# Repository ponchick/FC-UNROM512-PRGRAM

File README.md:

# FC-UNROM512

UNROM512 Famicom cartridge PCB (UNROM/UOROM family, extended PRG-ROM bank switching) with additional PRG RAM.

Russian version: [`README.ru.md`](README.ru.md)

More details about UNROM512 format and compatibility:

- [NESdev Wiki - UNROM 512](https://www.nesdev.org/wiki/UNROM_512)
- [NESdev Wiki mirror - UNROM 512](https://nesdev-wiki.nes.science/wikipages/UNROM_512.xhtml)

---

## Jumpers (board configuration)

### 1) Flash memory mode (write protection / self-flashing)

| Configuration | `FL1`-`FL4` | `FLASHABLE` | 74*139 | Bus conflicts |
| :--- | :---: | :---: | :---: | :---: |
| **Not Flashable** (write-protected) | Closed | Open | Not installed | **Present** |
| **Flashable** (self-flashable) | Open | Closed | Installed | **Absent** |

---

### 2) Mirroring

**Mirroring must match the ROM you are programming.** The game expects a specific mode (vertical/horizontal/1-screen). A wrong setting causes visual glitches.

Only one of these jumpers should be closed. For **Vertical mirroring**, close `VERT` and keep `HORIZ` and `ONE` open.

---

### 3) CHR RAM size configuration (8/16/32 KiB)

**The actual CHR RAM size is defined by the physical RAM chip** (for example, 62256 = 32 KiB). Jumpers only route the required address lines.

| Size | `8k` | `8k/16k` | `16k/32k` | `32k` |
| :--- | :---: | :---: | :---: | :---: |
| 8 KiB | Closed | Closed | Open | Open |
| 16 KiB | Open | Closed | Closed | Open |
| 32 KiB | Open | Open | Closed | Closed |

> **Use smaller CHR RAM sizes (8/16 KiB) only if the target ROM explicitly supports them.** Most UNROM512 / Mapper 30 software expects 32 KiB. Forcing a smaller size on unsupported ROMs can cause errors.

---

## License

This project is licensed under CERN Open Hardware Licence Version 2 - Permissive (`CERN-OHL-P-2.0`), see `LICENSE`.

SPDX-License-Identifier: `CERN-OHL-P-2.0`

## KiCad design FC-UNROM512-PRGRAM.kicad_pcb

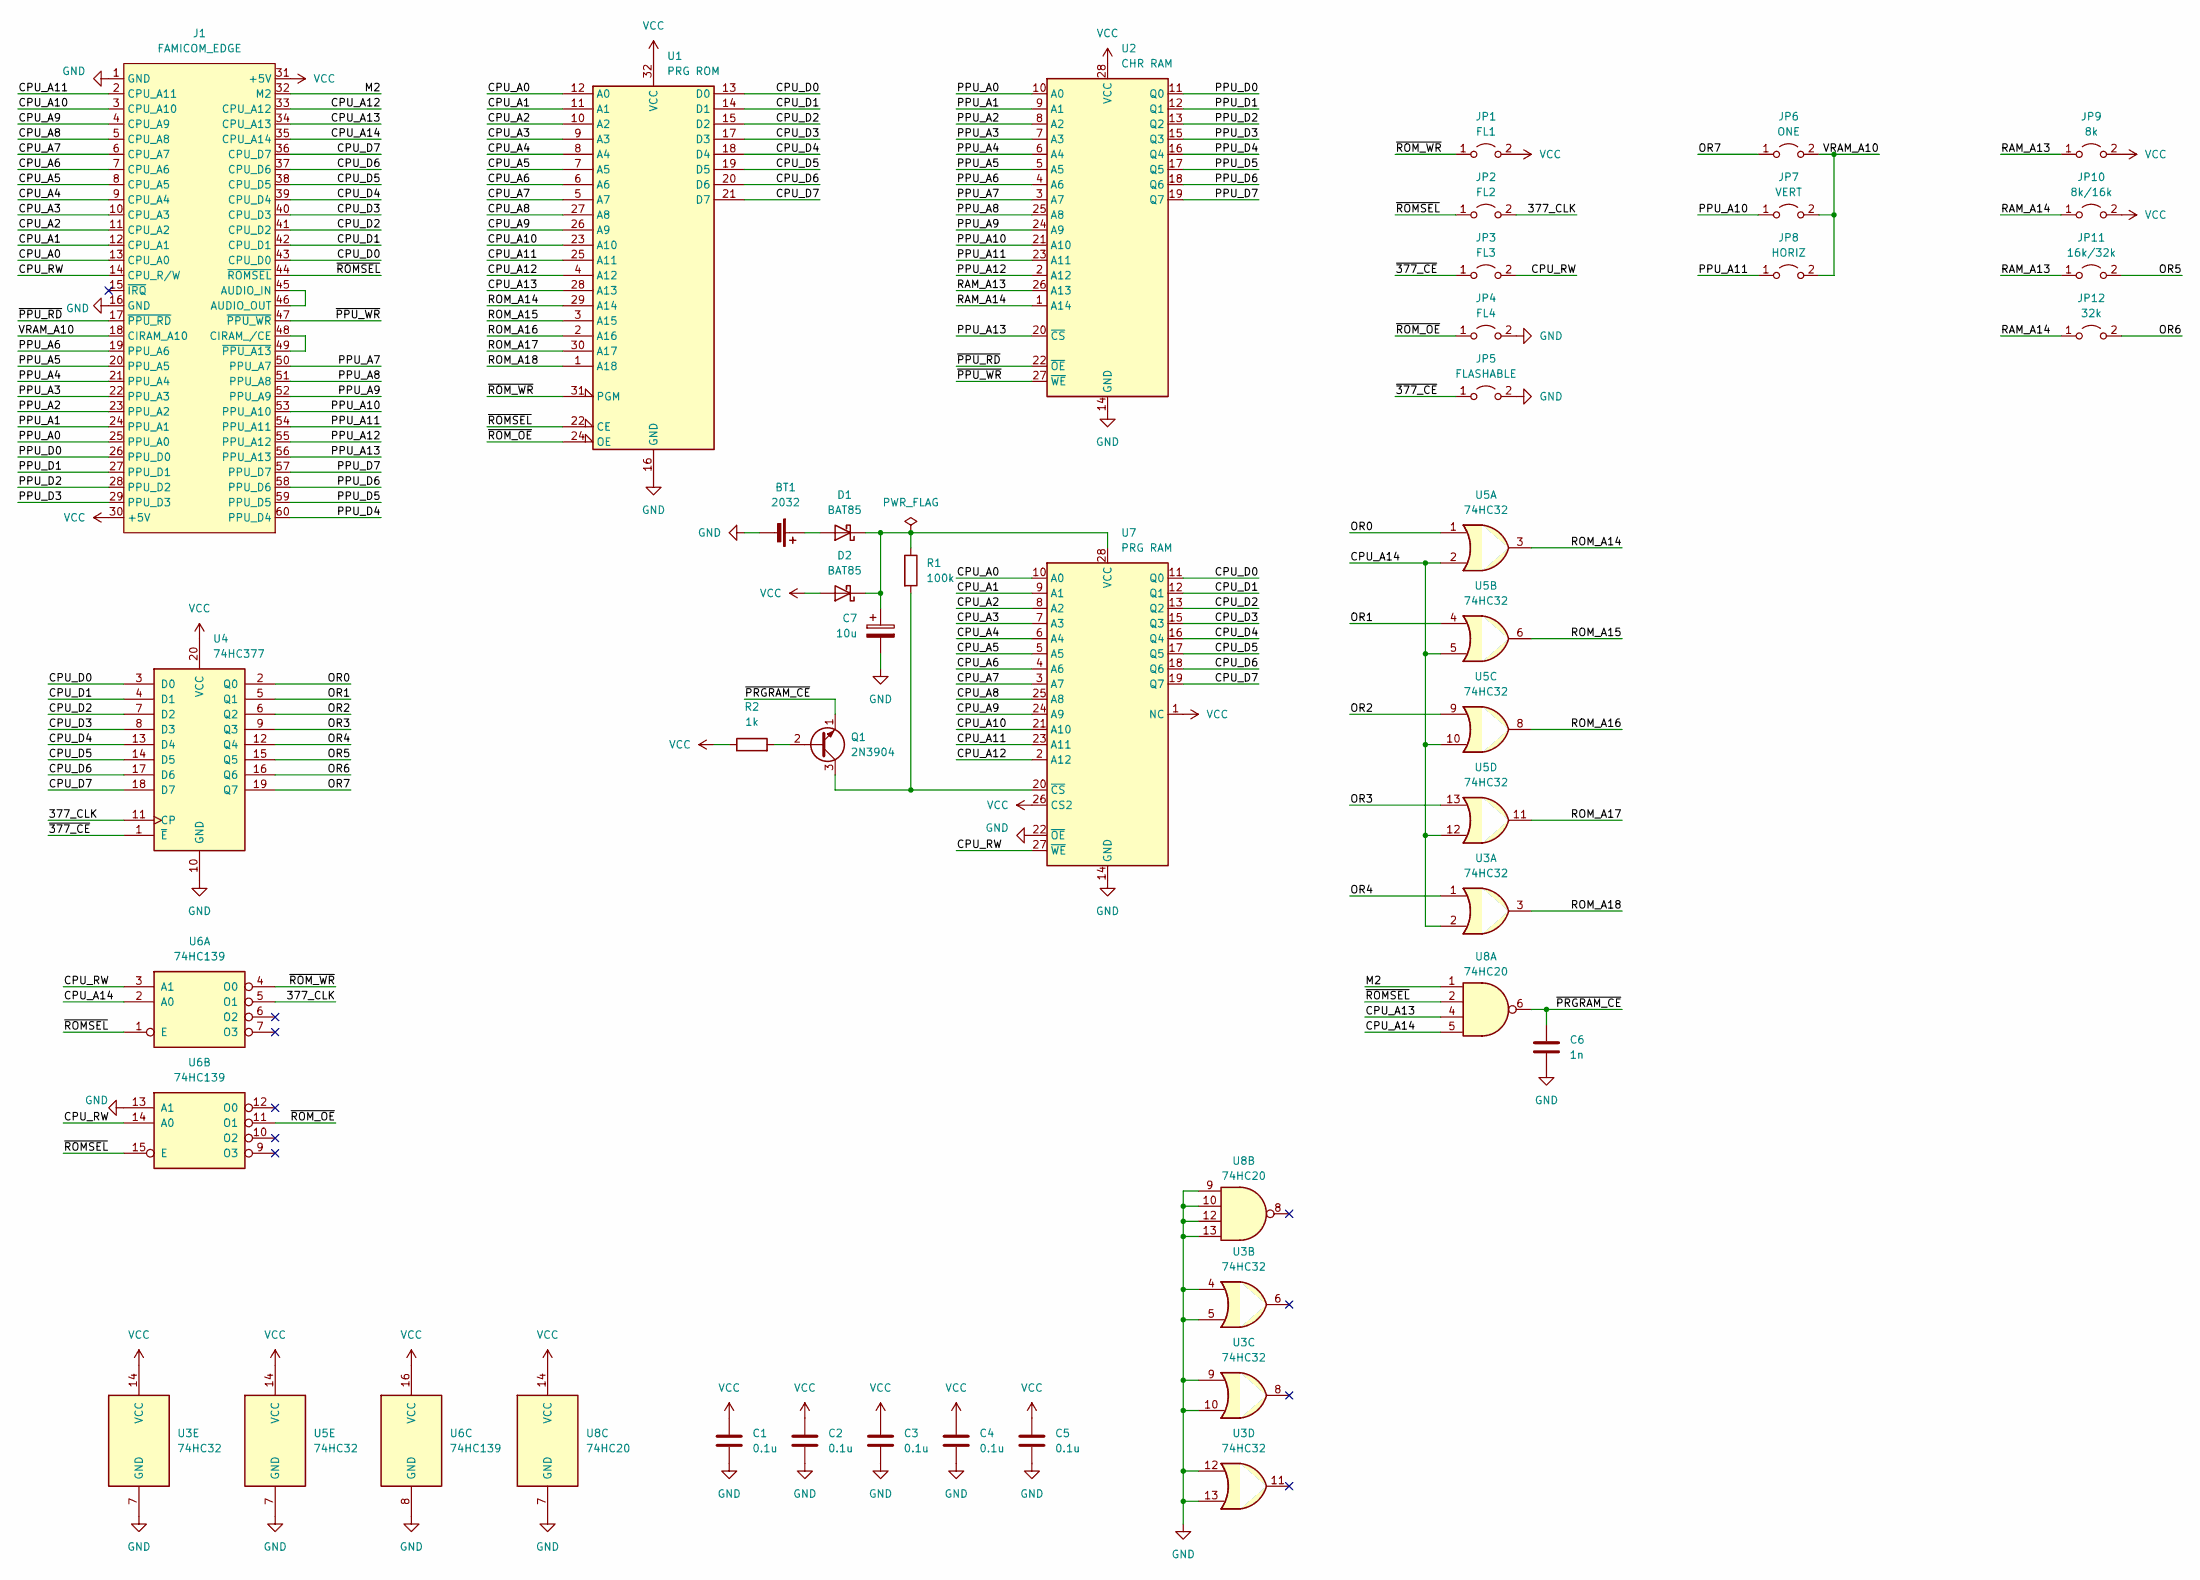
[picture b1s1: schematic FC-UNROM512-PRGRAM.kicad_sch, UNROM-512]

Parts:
BT1: 2032; BatteryHolder_Keystone_1060_1x2032
C1, C2, C3, C4, C5: 0.1u; C_Disc_D4.3mm_W1.9mm_P5.00mm
C6: 1n; C_Disc_D4.3mm_W1.9mm_P5.00mm
C7: 10u; CP_Radial_D4.0mm_P2.00mm
D1, D2: BAT85; D_DO-35_SOD27_P7.62mm_Horizontal
J1: FAMICOM_EDGE; CONN_EDGE_2x60
JP1: FL1; SolderJumper-2_P1.3mm_Open_Pad1.0x1.5mm
JP2: FL2; SolderJumper-2_P1.3mm_Open_Pad1.0x1.5mm
JP3: FL3; SolderJumper-2_P1.3mm_Open_Pad1.0x1.5mm
JP4: FL4; SolderJumper-2_P1.3mm_Open_Pad1.0x1.5mm
JP5: FLASHABLE; SolderJumper-2_P1.3mm_Open_Pad1.0x1.5mm
JP6: ONE; SolderJumper-2_P1.3mm_Open_Pad1.0x1.5mm
JP7: VERT; SolderJumper-2_P1.3mm_Open_Pad1.0x1.5mm
JP8: HORIZ; SolderJumper-2_P1.3mm_Open_Pad1.0x1.5mm
JP9: 8k; SolderJumper-2_P1.3mm_Open_Pad1.0x1.5mm
JP10: 8k/16k; SolderJumper-2_P1.3mm_Open_Pad1.0x1.5mm
JP11: 16k/32k; SolderJumper-2_P1.3mm_Open_Pad1.0x1.5mm
JP12: 32k; SolderJumper-2_P1.3mm_Open_Pad1.0x1.5mm
Q1: 2N3904; TO-92_Inline_Wide
R1: 100k; R_Axial_DIN0204_L3.6mm_D1.6mm_P7.62mm_Horizontal
R2: 1k; R_Axial_DIN0204_L3.6mm_D1.6mm_P7.62mm_Horizontal
U1: PRG ROM; DIP-32_W15.24mm_Socket
U2: CHR RAM; DIP-28_Dual
U3, U5: 74HC32; DIP-14_W7.62mm
U4: 74HC377; DIP-20_W7.62mm
U6: 74HC139; DIP-16_W7.62mm
U7: PRG RAM; DIP-28_Dual
U8: 74HC20; DIP-14_W7.62mm

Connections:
/377_CLK: JP2.2 (B), U4.11 (CP), U6.5 (O1)
/CPU_A0: J1.13 (CPU_A0), U1.12 (A0), U7.10 (A0)
/CPU_A1: J1.12 (CPU_A1), U1.11 (A1), U7.9 (A1)
/CPU_A2: J1.11 (CPU_A2), U1.10 (A2), U7.8 (A2)
/CPU_A3: J1.10 (CPU_A3), U1.9 (A3), U7.7 (A3)
/CPU_A4: J1.9 (CPU_A4), U1.8 (A4), U7.6 (A4)
/CPU_A5: J1.8 (CPU_A5), U1.7 (A5), U7.5 (A5)
/CPU_A6: J1.7 (CPU_A6), U1.6 (A6), U7.4 (A6)
/CPU_A7: J1.6 (CPU_A7), U1.5 (A7), U7.3 (A7)
/CPU_A8: J1.5 (CPU_A8), U1.27 (A8), U7.25 (A8)
/CPU_A9: J1.4 (CPU_A9), U1.26 (A9), U7.24 (A9)
/CPU_A10: J1.3 (CPU_A10), U1.23 (A10), U7.21 (A10)
/CPU_A11: J1.2 (CPU_A11), U1.25 (A11), U7.23 (A11)
/CPU_A12: J1.33 (CPU_A12), U1.4 (A12), U7.2 (A12)
/CPU_A13: J1.34 (CPU_A13), U1.28 (A13), U8.4
/CPU_A14: J1.35 (CPU_A14), U3.2, U5.2, U5.5, U5.10, U5.12, U6.2 (A0), U8.5
/CPU_D0: J1.43 (CPU_D0), U1.13 (D0), U4.3 (D0), U7.11 (Q0)
/CPU_D1: J1.42 (CPU_D1), U1.14 (D1), U4.4 (D1), U7.12 (Q1)
/CPU_D2: J1.41 (CPU_D2), U1.15 (D2), U4.7 (D2), U7.13 (Q2)
/CPU_D3: J1.40 (CPU_D3), U1.17 (D3), U4.8 (D3), U7.15 (Q3)
/CPU_D4: J1.39 (CPU_D4), U1.18 (D4), U4.13 (D4), U7.16 (Q4)
/CPU_D5: J1.38 (CPU_D5), U1.19 (D5), U4.14 (D5), U7.17 (Q5)
/CPU_D6: J1.37 (CPU_D6), U1.20 (D6), U4.17 (D6), U7.18 (Q6)
/CPU_D7: J1.36 (CPU_D7), U1.21 (D7), U4.18 (D7), U7.19 (Q7)
/CPU_RW: J1.14 (CPU_R/W), JP3.2 (B), U6.3 (A1), U6.14 (A0), U7.27 (~WE)
/M2: J1.32 (M2), U8.1
/OR0: U4.2 (Q0), U5.1
/OR1: U4.5 (Q1), U5.4
/OR2: U4.6 (Q2), U5.9
/OR3: U4.9 (Q3), U5.13
/OR4: U3.1, U4.12 (Q4)
/OR5: JP11.2 (B), U4.15 (Q5)
/OR6: JP12.2 (B), U4.16 (Q6)
/OR7: JP6.1 (A), U4.19 (Q7)
/PPU_A0: J1.25 (PPU_A0), U2.10 (A0)
/PPU_A1: J1.24 (PPU_A1), U2.9 (A1)
/PPU_A2: J1.23 (PPU_A2), U2.8 (A2)
/PPU_A3: J1.22 (PPU_A3), U2.7 (A3)
/PPU_A4: J1.21 (PPU_A4), U2.6 (A4)
/PPU_A5: J1.20 (PPU_A5), U2.5 (A5)
/PPU_A6: J1.19 (PPU_A6), U2.4 (A6)
/PPU_A7: J1.50 (PPU_A7), U2.3 (A7)
/PPU_A8: J1.51 (PPU_A8), U2.25 (A8)
/PPU_A9: J1.52 (PPU_A9), U2.24 (A9)
/PPU_A10: J1.53 (PPU_A10), JP7.1 (A), U2.21 (A10)
/PPU_A11: J1.54 (PPU_A11), JP8.1 (A), U2.23 (A11)
/PPU_A12: J1.55 (PPU_A12), U2.2 (A12)
/PPU_A13: J1.56 (PPU_A13), U2.20 (~CS)
/PPU_D0: J1.26 (PPU_D0), U2.11 (Q0)
/PPU_D1: J1.27 (PPU_D1), U2.12 (Q1)
/PPU_D2: J1.28 (PPU_D2), U2.13 (Q2)
/PPU_D3: J1.29 (PPU_D3), U2.15 (Q3)
/PPU_D4: J1.60 (PPU_D4), U2.16 (Q4)
/PPU_D5: J1.59 (PPU_D5), U2.17 (Q5)
/PPU_D6: J1.58 (PPU_D6), U2.18 (Q6)
/PPU_D7: J1.57 (PPU_D7), U2.19 (Q7)
/RAM_A13: JP9.1 (A), JP11.1 (A), U2.26 (A13)
/RAM_A14: JP10.1 (A), JP12.1 (A), U2.1 (A14)
/ROM_A14: U1.29 (A14), U5.3
/ROM_A15: U1.3 (A15), U5.6
/ROM_A16: U1.2 (A16), U5.8
/ROM_A17: U1.30 (A17), U5.11
/ROM_A18: U1.1 (A18), U3.3
/VRAM_A10: J1.18 (CIRAM_A10), JP6.2 (B), JP7.2 (B), JP8.2 (B)
/~377_CE: JP3.1 (A), JP5.1 (A), U4.1 (~E)
/~PPU_RD: J1.17 (~PPU_RD), U2.22 (~OE)
/~PPU_WR: J1.47 (~PPU_WR), U2.27 (~WE)
/~PRGRAM_CE: C6.1, Q1.1 (E), U8.6
/~ROMSEL: J1.44 (~ROMSEL), JP2.1 (A), U1.22 (CE), U6.1 (E), U6.15 (E), U8.2
/~ROM_OE: JP4.1 (A), U1.24 (OE), U6.11 (O1)
/~ROM_WR: JP1.1 (A), U1.31 (PGM), U6.4 (O0)
GND: BT1.2 (-), C1.2, C2.2, C3.2, C4.2, C5.2, C6.2, C7.2, J1.1 (GND), J1.16 (GND), JP4.2 (B), JP5.2 (B), U1.16 (GND), U2.14 (GND), U3.4, U3.5, U3.7 (GND), U3.9, U3.10, U3.12, U3.13, U4.10 (GND), U5.7 (GND), U6.8 (GND), U6.13 (A1), U7.14 (GND), U7.22 (~OE), U8.7 (GND), U8.9, U8.10, U8.12, U8.13
unnamed: BT1.1 (+), D1.2 (A)
unnamed: C7.1, D1.1 (K), D2.1 (K), R1.1, U7.28 (VCC)
unnamed: J1.45 (AUDIO_IN), J1.46 (AUDIO_OUT)
unnamed: J1.48 (CIRAM_/CE), J1.49 (~PPU_A13)
unnamed: Q1.2 (B), R2.2
unnamed: Q1.3 (C), R1.2, U7.20 (~CS)
VCC: C1.1, C2.1, C3.1, C4.1, C5.1, D2.2 (A), J1.30 (+5V), J1.31 (+5V), JP1.2 (B), JP9.2 (B), JP10.2 (B), R2.1, U1.32 (VCC), U2.28 (VCC), U3.14 (VCC), U4.20 (VCC), U5.14 (VCC), U6.16 (VCC), U7.1 (NC), U7.26 (CS2), U8.14 (VCC)

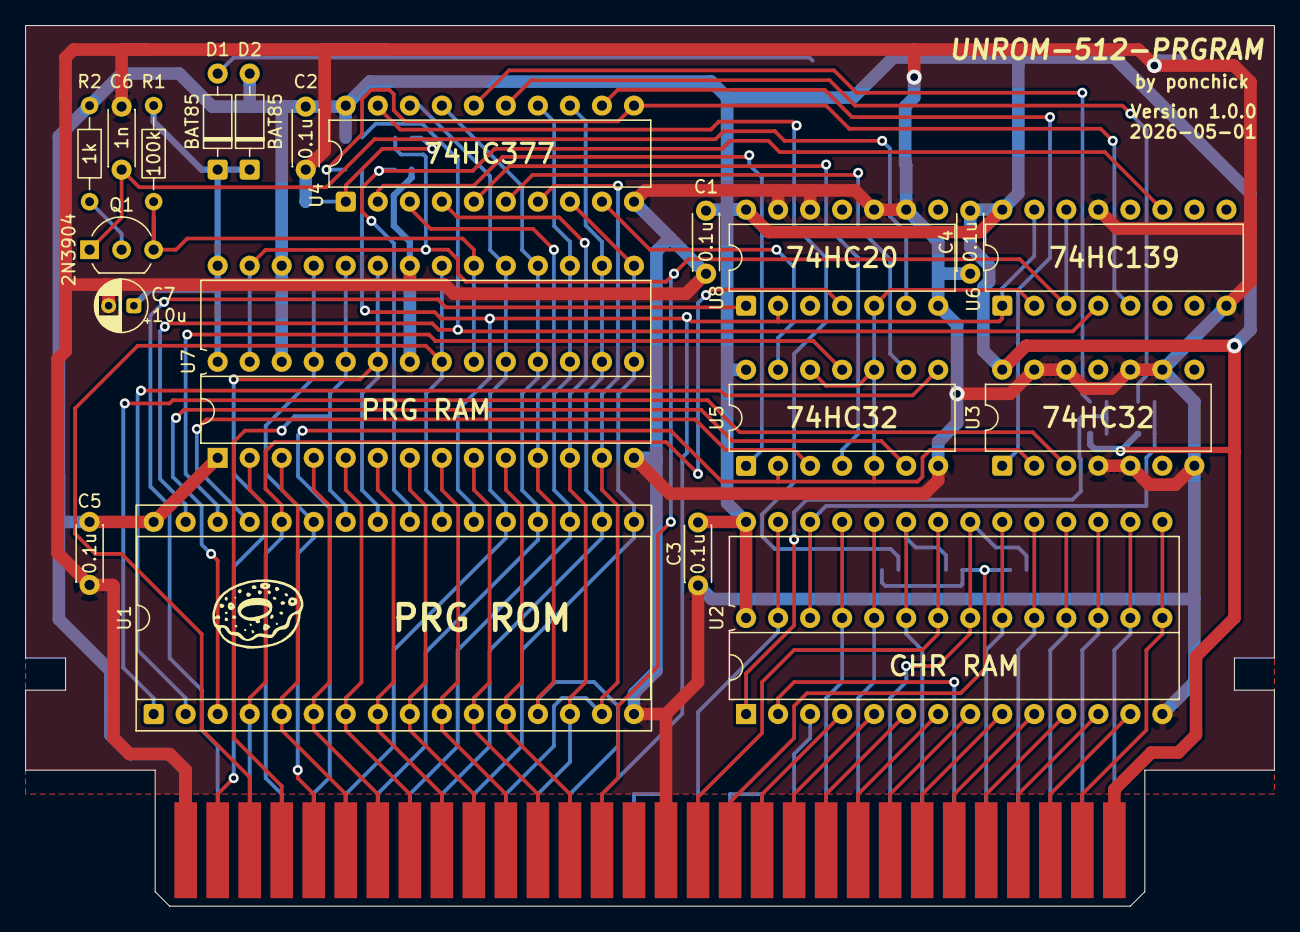
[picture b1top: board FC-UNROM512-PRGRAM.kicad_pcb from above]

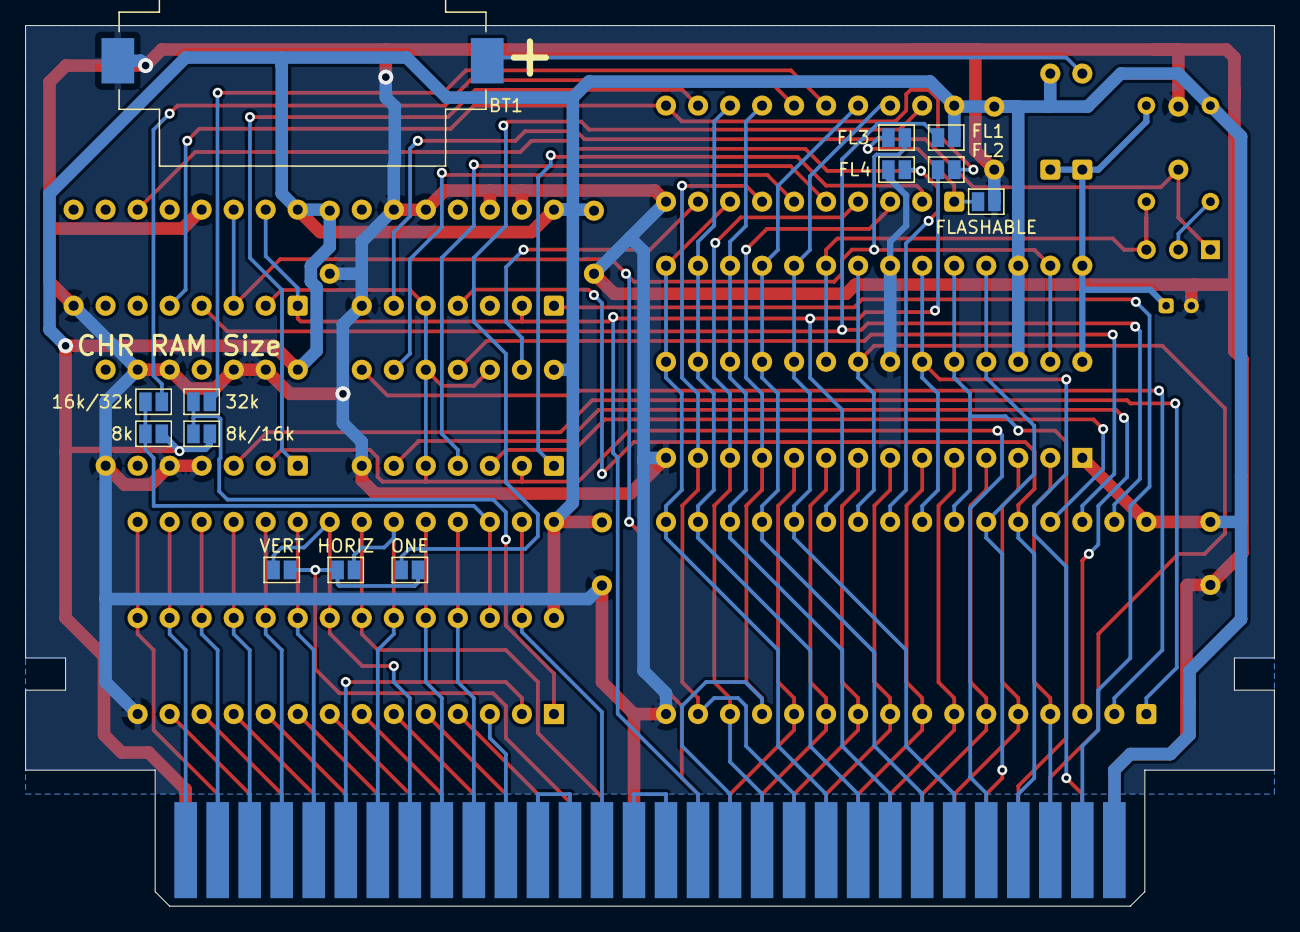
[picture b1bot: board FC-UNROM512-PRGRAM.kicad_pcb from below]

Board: 2 copper layers, 99.1 x 69.8 mm, 35 parts (13 on the bottom side), 79 nets.

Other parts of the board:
LOGO#: LOGO; ponchick

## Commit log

2026-05-01 Initial release
2026-05-01 Update russian README
2026-05-01 Schematic attributes update
